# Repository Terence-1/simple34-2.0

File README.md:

# simple34 2.0
another wireless only 34 key split keyboard using my old matrix setup with splay.

Inspired by: [raii](https://github.com/unspecworks/raii-wireless) and [klotz](https://github.com/GEIGEIGEIST/KLOTZ)

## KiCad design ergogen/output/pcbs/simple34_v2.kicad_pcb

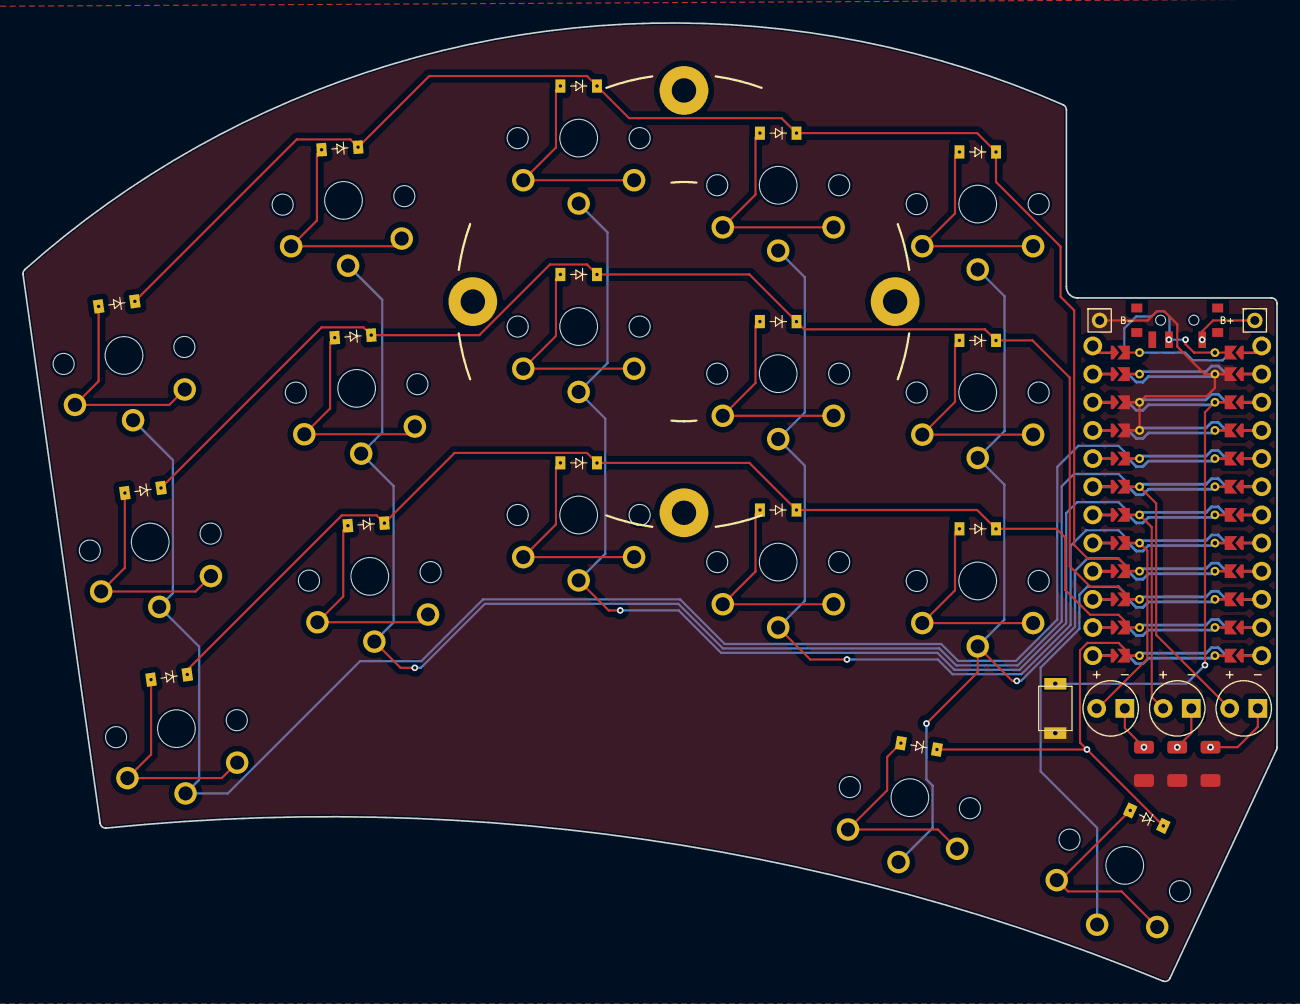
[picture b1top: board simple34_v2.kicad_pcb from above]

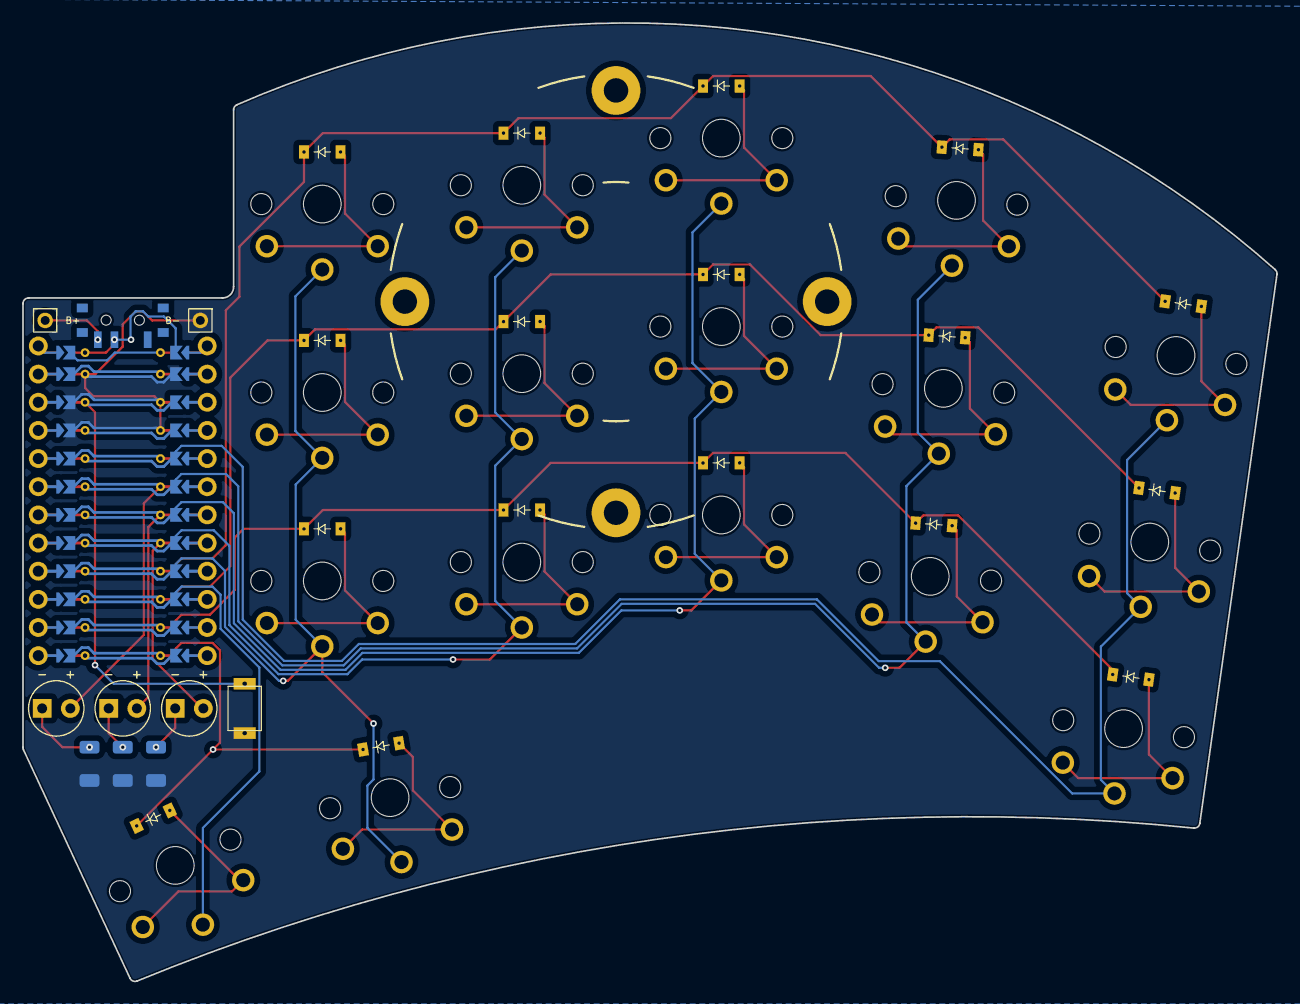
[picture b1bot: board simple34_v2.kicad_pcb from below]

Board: 2 copper layers, 113.1 x 86.5 mm, 45 parts (18 on the bottom side), 37 nets.

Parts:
BAT1: battery_socket_tht
D1, D2, D3, D4, D5, D6, D7, D8, D9, D10, D11, D12, D13, D14, D15, D16, D17: diode_tht_sod123
LED1, LED2, LED3: led_5mm_tht
MCU1: mcu_supermini_nrf52840
PWR1: power_switch_smd_side
R1, R2, R3: resistor_1206
S1, S2, S3, S4, S5, S6, S7, S8, S9, S10, S11, S12, S13, S14, S15, S16, S17: switch_choc_v1_v2
SW1: reset_smd
TP1: Tenting Puck, no hole; TentingPuck_NoHole

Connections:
BAT_P: BAT1.2, PWR1.1, PWR1.3
C0: MCU1.105, S1.2, S2.2, S3.2
C1: MCU1.106, S4.2, S5.2, S6.2
C2: MCU1.107, S7.2, S8.2, S9.2
C3: MCU1.108, S10.2, S11.2, S12.2
C4: MCU1.109, S13.2, S14.2, S15.2, S16.2
C5: MCU1.110, S17.2
GND: BAT1.1, MCU1.102, MCU1.121, MCU1.122, R1.2, R2.2, R3.2, SW1.1
R0: D3.1, D6.1, D9.1, D12.1, D15.1, MCU1.116
R1: D2.1, D5.1, D8.1, D11.1, D14.1, MCU1.115
R2: D1.1, D4.1, D7.1, D10.1, D13.1, MCU1.114
R3: D16.1, D17.1, MCU1.113
RAW: MCU1.101, PWR1.2
RST: MCU1.103, SW1.2
first_only: D16.2, S16.1
index_bottom: D10.2, S10.1
index_home: D11.2, S11.1
index_top: D12.2, S12.1
inner_bottom: D13.2, S13.1
inner_home: D14.2, S14.1
inner_top: D15.2, S15.1
led_1: LED1.2, MCU1.119
led_2: LED2.2, MCU1.118
led_3: LED3.2, MCU1.117
middle_bottom: D7.2, S7.1
middle_home: D8.2, S8.1
middle_top: D9.2, S9.1
pinky_bottom: D1.2, S1.1
pinky_home: D2.2, S2.1
pinky_top: D3.2, S3.1
r1: LED1.1, R1.1
r2: LED2.1, R2.1
r3: LED3.1, R3.1
ring_bottom: D4.2, S4.1
ring_home: D5.2, S5.1
ring_top: D6.2, S6.1
second_only: D17.2, S17.1

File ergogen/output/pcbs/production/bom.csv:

Designator,Footprint,Quantity,Value,LCSC Part #
BAT1,battery_socket_tht,1,,
"D1, D10, D11, D12, D13, D14, D15, D16, D17, D2, D3, D4, D5, D6, D7, D8, D9",diode_tht_sod123,17,,
"LED1, LED2, LED3",led_5mm_tht,3,,
PWR1,power_switch_smd_side,1,,
"R1, R2, R3",resistor_1206,3,,
SW1,reset_smd,1,,

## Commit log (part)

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2026-05-05 pre-print
2026-05-05 yeah...
2026-05-05 rmk 2
2026-05-07 OH MY, ARCS EXISTS
2026-05-07 i forgot to save
2026-05-12 case fillet
2026-05-13 huge change
2026-05-14 LARGE UPDATE
2026-05-14 non-slip
2026-05-14 stands
2026-05-17 lil change
2026-05-17 non slip again
2026-05-18 another change
2026-05-18 no more qmk
